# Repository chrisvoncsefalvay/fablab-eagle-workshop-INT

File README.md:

# FabLab EAGLE workshop (INTRODUCTORY)
The official repo for the Munich Fablab EAGLE introductory course 

## The board
The board used to demonstrate EAGLE's functionality is a small ATtiny based brake light tester. The general idea is as follows. Upon resetting the device, an ambient light measurement is taken for five seconds. At the end of the five seconds, you must have attached the device to your light. The device then enters measurement mode. The LED will light up red and turn green if and only if the brake light has lit up. After 60 seconds of no signal, the device will enter sleep. 

### Specs
The device must accommodate the ATtiny, an I2C based light sensor, a battery, a tricolour LED, a power management circuit and all else that's needed for the board's functioning.

The board is driven by three 3V CR927 batteries in series, yielding 9V. This is converted to 5V by the LDO (U2).

Most of the heavy lifting is done by the MCU. The MCU has to be programmable through ICSP headers, though these will not necessarily be mounted in production devices (potentially replaced by a pogo/bed of nails approach).

### Implementation

This is a possible implementation, but not the only possible implementation. Be creative, use your mind.

### Board design considerations
The usual considerations apply, but don't forget to
- leave enough space,
- provide fiducials and mount holes,
- use largeish components (1206/1210) and large pads for hand soldering ('W pads') where available,
- stick to two layers, and
- avoid the autorouter.

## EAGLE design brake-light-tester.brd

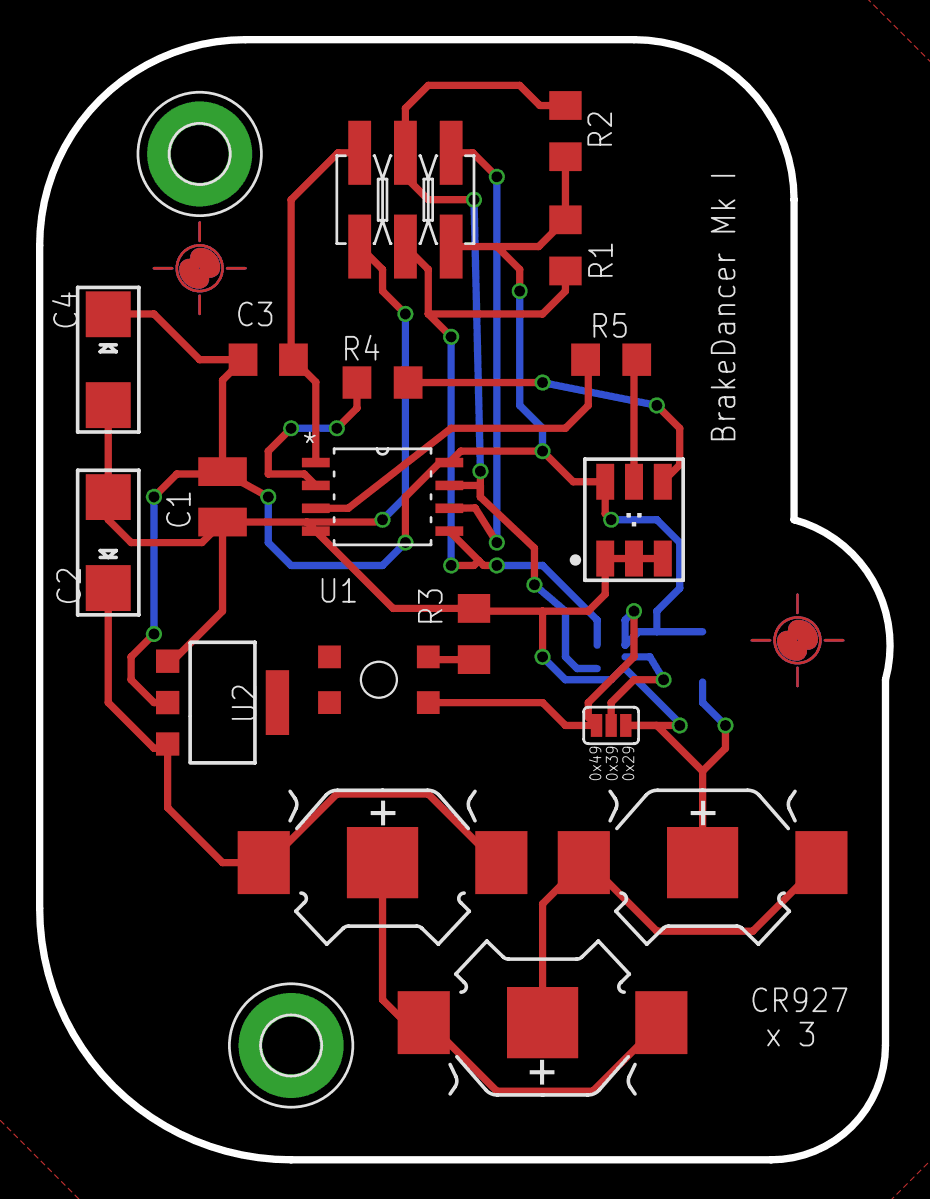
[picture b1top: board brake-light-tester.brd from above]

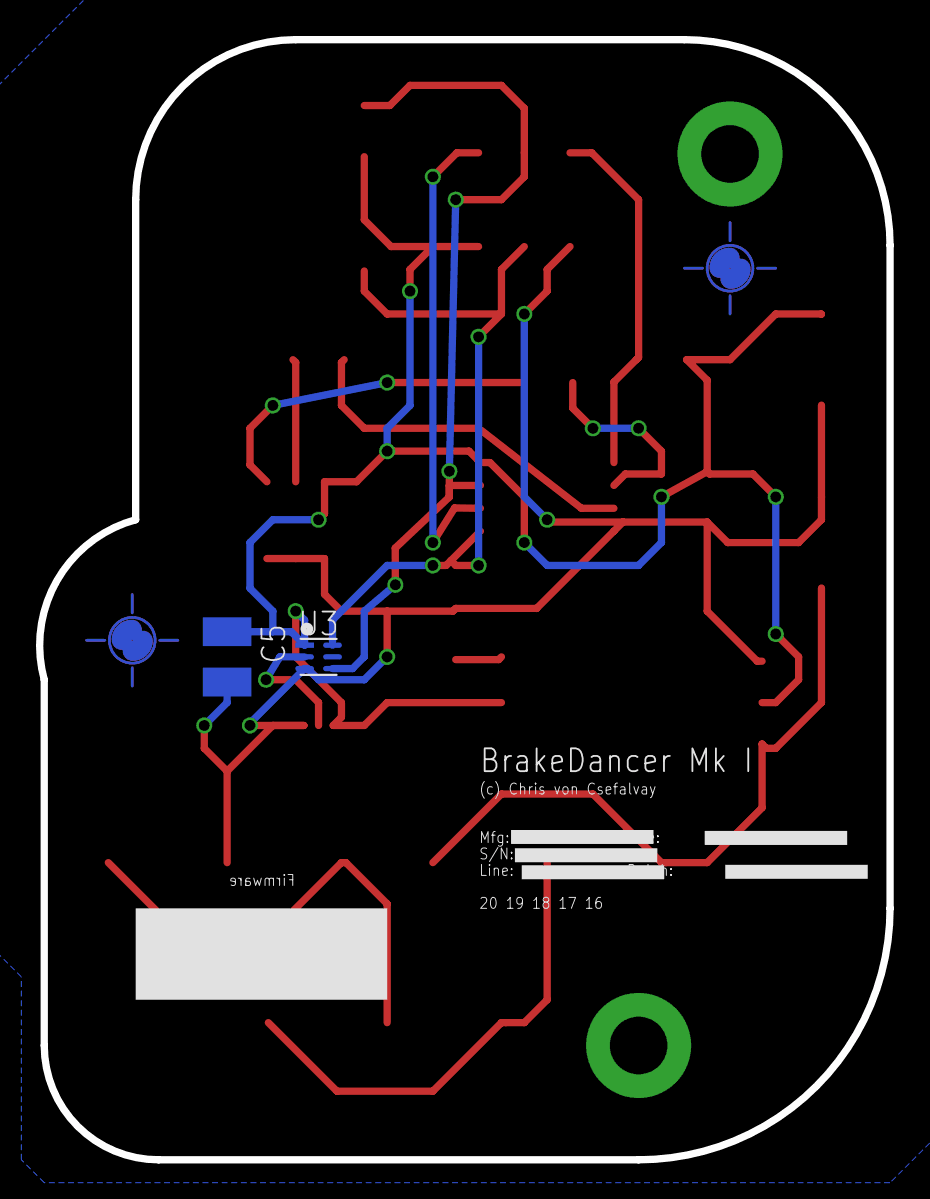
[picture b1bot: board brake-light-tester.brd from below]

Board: 2 copper layers, 47.2 x 62.2 mm, 25 parts (2 on the bottom side), 15 nets.

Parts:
C1, C5: 0.1uF; C1210
C2, C4: 10uF; EIA6032-28/C-R
C3: 0.1uF; C1206
DRILEGEND: DRILEGEND
FID1, FID2: FIDUCIALROUND; PASS-ROUND
G1, G2, G3: 10MM_SM_COIN_CELL_CLIP
H1, H2: MOUNT-PAD-ROUND3.2; 3,2-PAD
J1: CON_HEADER_PRG_AVR_ICSP-SMD; M2X3_SMD
LED1: RGBLED_PLCC6
R1, R2: 4k7; R1206
R3: 10k; R1206
R4: 68R; R1206
R5: 56R; R1206
SJ1: SJ_3_PASTE1&2
SW1: TACTILE-SWITCH-7914G; 7914G
U1: ATTINY85-20SU; SOIC127P798X216-8N
U2: LM1117/5V; SOT223-R
U3: TSL2561FN; FN-6

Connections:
+5V: C1.1, C3.1, C4.+, C5.1, J1.2, LED1.6, R1.2, R2.2, SJ1.1, SW1.1, U1.8, U2.2, U3.1
GND: C1.2, C2.-, C4.-, C5.2, G1.-, J1.6, LED1.1, LED1.2, LED1.3, R3.2, SJ1.3, U1.4, U2.1, U3.3
unnamed: C2.+, G3.+@1, G3.+@2, U2.3
unnamed: SJ1.2, U3.2
unnamed: LED1.4, R4.1
unnamed: LED1.5, R5.2
unnamed: G1.+@1, G1.+@2, G2.-
unnamed: G2.+@1, G2.+@2, G3.-
unnamed: R3.1, SW1.3
PB0: J1.4, R1.1, U1.5, U3.6
PB1: J1.1, U1.6
PB2: J1.3, R2.1, U1.7, U3.4
PB3: R4.2, U1.2
PB4: R5.1, U1.3
PB5: C3.2, J1.5, U1.1

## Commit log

2016-01-04 Initial commit of completed schematic.
2016-01-04 Board generated.
2016-01-04 Components laid out but unrouted.
2016-01-04 Manually routed PCB, first iteration.
2016-01-04 External dimension margins fixed (layer Dimensions).
2016-01-04 Top layer GND pour.
2016-01-04 Bottom layer GND pour.
2016-01-04 Measurements.
2016-01-04 Component name silk screen fix.
2016-01-04 Final version with silkscreens.
2016-01-04 Added drill legend.
2016-01-04 Replaced 1210 caps with 1206s as they are much more available.
2016-01-04 Now includes BOM.
2016-01-04 T/B images for reference.
2016-01-04 Now includes schematic image.

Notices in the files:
parts and their libraries:
microbuilder: This work is placed in the public domain, and may be freely used for commercial and non-commercial work with the following conditions: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
SparkFun-Retired: Licensing:Creative Commons ShareAlike 4.0 International - https://creativecommons.org/licenses/by-sa/4.0
